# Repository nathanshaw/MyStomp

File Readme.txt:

ReadMe file for the MyStomp Project

To Do :

Flags to use 

--dac:3
--adc:3
--c1
--adaptive:256
--srate 44100

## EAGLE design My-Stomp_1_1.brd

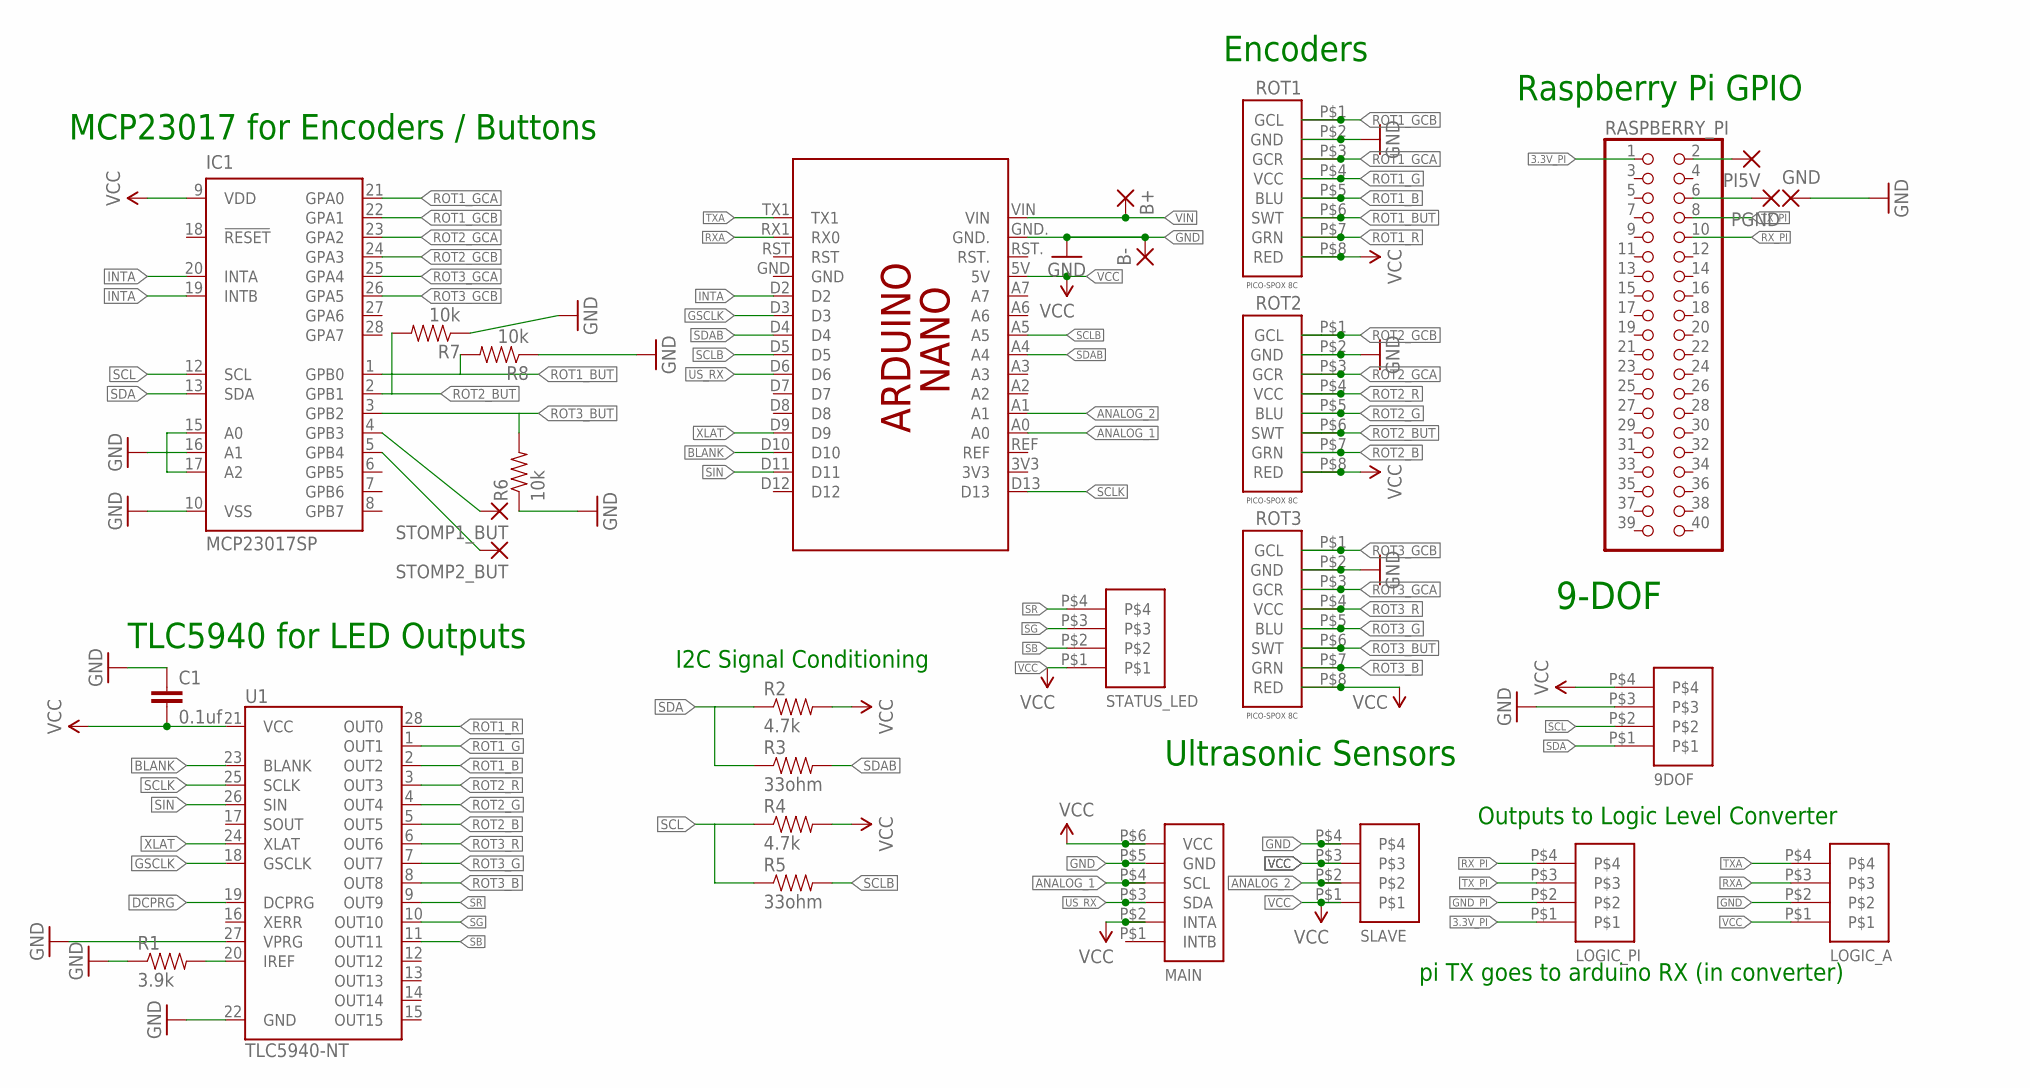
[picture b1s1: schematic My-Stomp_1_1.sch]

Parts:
9DOF: PICO_SPOX_4C
B+: 2,15/1,0
B-: 2,15/1,0
C1: 0.1uf; CAP-PTH-5MM
GND: 2,15/1,0
IC1: MCP23017SP; DIL28-3
LOGIC_A: PICO_SPOX_4C
LOGIC_PI: PICO_SPOX_4C
MAIN: PICO_SPOX_6C
PCB2: ARDUINO_NANO
PGND: 2,15/1,0
PI5V: 2,15/1,0
R1: 3.9k; AXIAL-0.3
R2, R4: 4.7k; AXIAL-0.3
R3, R5: 33ohm; AXIAL-0.3
R6, R7, R8: 10k; AXIAL-0.3
RASPBERRY_PI: PINHD-2X20; 2X20
ROT1, ROT2, ROT3: PICO_SPOX_8C; PICO_SPOC_8C
SLAVE: PICO_SPOX_4C
STATUS_LED: PICO_SPOX_4C
STOMP1_BUT, STOMP2_BUT: 2,15/1,0
U1: TLC5940-NT; DIL28-3

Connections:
3.3V_PI: LOGIC_PI.P$1, RASPBERRY_PI.1
ANALOG_1: MAIN.P$4 (SCL), PCB2.A0
ANALOG_2: PCB2.A1, SLAVE.P$2
BLANK: PCB2.D10, U1.23 (BLANK)
DCPRG: U1.19 (DCPRG)
GND: 9DOF.P$3, B-.1, C1.1, GND.1, IC1.10 (VSS), IC1.15 (A0), IC1.16 (A1), IC1.17 (A2), LOGIC_A.P$2, MAIN.P$5 (GND), PCB2.GND., R1.P$1 (1), R6.P$1 (1), R7.P$1 (1), R8.P$1 (1), ROT1.P$2 (GND), ROT2.P$2 (GND), ROT3.P$2 (GND), SLAVE.P$4, U1.22 (GND), U1.27 (VPRG)
GND_PI: LOGIC_PI.P$2, PGND.1, RASPBERRY_PI.6
GSCLK: PCB2.D3, U1.18 (GSCLK)
INTA: IC1.19 (INTB), IC1.20 (INTA), PCB2.D2
unnamed: IC1.4 (GPB3), STOMP1_BUT.1
unnamed: IC1.5 (GPB4), STOMP2_BUT.1
unnamed: PI5V.1, RASPBERRY_PI.2
unnamed: R1.P$2 (2), U1.20 (IREF)
ROT1_B: ROT1.P$5 (BLU), U1.2 (OUT2)
ROT1_BUT: IC1.1 (GPB0), R8.P$2 (2), ROT1.P$6 (SWT)
ROT1_G: ROT1.P$4 (VCC), U1.1 (OUT1)
ROT1_GCA: IC1.21 (GPA0), ROT1.P$3 (GCR)
ROT1_GCB: IC1.22 (GPA1), ROT1.P$1 (GCL)
ROT1_R: ROT1.P$7 (GRN), U1.28 (OUT0)
ROT2_B: ROT2.P$7 (GRN), U1.5 (OUT5)
ROT2_BUT: IC1.2 (GPB1), R7.P$2 (2), ROT2.P$6 (SWT)
ROT2_G: ROT2.P$5 (BLU), U1.4 (OUT4)
ROT2_GCA: IC1.23 (GPA2), ROT2.P$3 (GCR)
ROT2_GCB: IC1.24 (GPA3), ROT2.P$1 (GCL)
ROT2_R: ROT2.P$4 (VCC), U1.3 (OUT3)
ROT3_B: ROT3.P$7 (GRN), U1.8 (OUT8)
ROT3_BUT: IC1.3 (GPB2), R6.P$2 (2), ROT3.P$6 (SWT)
ROT3_G: ROT3.P$5 (BLU), U1.7 (OUT7)
ROT3_GCA: IC1.25 (GPA4), ROT3.P$3 (GCR)
ROT3_GCB: IC1.26 (GPA5), ROT3.P$1 (GCL)
ROT3_R: ROT3.P$4 (VCC), U1.6 (OUT6)
RXA: LOGIC_A.P$3, PCB2.RX1 (RX0)
RX_PI: LOGIC_PI.P$4, RASPBERRY_PI.10
SB: STATUS_LED.P$2, U1.11 (OUT11)
SCL: 9DOF.P$2, IC1.12 (SCL), R4.P$1 (1), R5.P$1 (1)
SCLB: PCB2.A5, PCB2.D5, R5.P$2 (2)
SCLK: PCB2.D13, U1.25 (SCLK)
SDA: 9DOF.P$1, IC1.13 (SDA), R2.P$1 (1), R3.P$1 (1)
SDAB: PCB2.A4, PCB2.D4, R3.P$2 (2)
SG: STATUS_LED.P$3, U1.10 (OUT10)
SIN: PCB2.D11, U1.26 (SIN)
SR: STATUS_LED.P$4, U1.9 (OUT9)
TXA: LOGIC_A.P$4, PCB2.TX1
TX_PI: LOGIC_PI.P$3, RASPBERRY_PI.8
US_RX: MAIN.P$3 (SDA), PCB2.D6
VCC: 9DOF.P$4, C1.2, IC1.9 (VDD), LOGIC_A.P$1, MAIN.P$2 (INTA), MAIN.P$6 (VCC), PCB2.5V, R2.P$2 (2), R4.P$2 (2), ROT1.P$8 (RED), ROT2.P$8 (RED), ROT3.P$8 (RED), SLAVE.P$1, SLAVE.P$3, STATUS_LED.P$1, U1.21 (VCC)
VIN: B+.1, PCB2.VIN
XLAT: PCB2.D9, U1.24 (XLAT)

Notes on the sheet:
I2C Signal Conditioning
TLC5940 for LED Outputs
MCP23017 for Encoders / Buttons
Ultrasonic Sensors
9-DOF
pi TX goes to arduino RX (in converter)
Outputs to Logic Level Converter
Raspberry Pi GPIO
Encoders

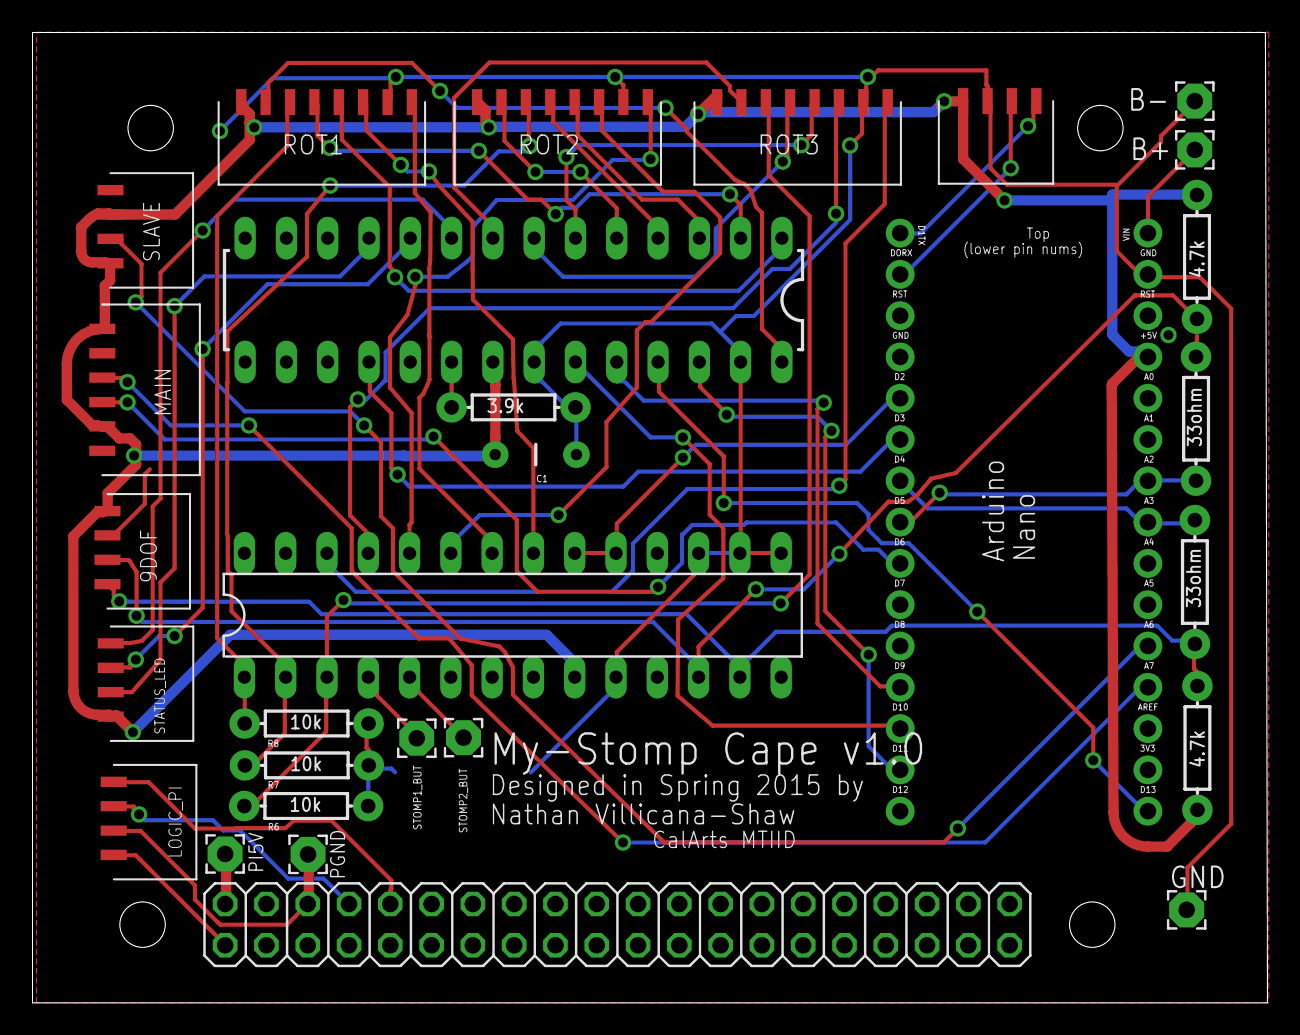
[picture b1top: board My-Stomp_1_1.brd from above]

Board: 2 copper layers, 76.0 x 59.7 mm, 29 parts (0 on the bottom side), 47 nets.

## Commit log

2015-02-09 Basic Framework for FX added
2015-02-09 Sewing things together more, added recording
2015-02-09 Everything Works, Stable Build
2015-02-09 Added 3d models and presentations
2015-02-09 Finished Presentation
2015-02-09 Added images for presentations and more
2015-02-23 Added Firmware folder
2015-02-23 test script added for FX
2015-02-23 Code for Ultrasonics Updated
    need to apply medium filter to ultrasonics for better readings
2015-02-23 Added MCP test file (untested)
2015-02-23 Another test file
2015-02-23 tweaked firmware a bit
2015-02-24 Crosstalk Folder and Code Added
    The crosstalk folder is for sketches that test the arduino/raspberry pi
    communication loop
2015-02-24 added spin test code
2015-02-24 added Readme file and got git on pi working
2015-02-24 9dof firmware added
2015-02-25 Untested mcl code added
2015-02-25 added working mcl code
2015-02-26 added more code
2015-02-27 code to test encoders added
2015-02-28 Started Master Code
    With startup modes
2015-03-01 Started Merging Code
2015-03-02 Got working modes
    for boot and long pressed and controller upside down
2015-03-03 Clean-up
    got rid of outdated code
2015-03-04 added pi test code
2015-03-04 got working pi code - for testing
2015-03-04 fix a bug
2015-03-07 tweaking
2015-03-07 Sound is Flowing
2015-03-07 program 1 is clean and reverb
2015-03-07 fixed bug
2015-03-07 bug fix again
2015-03-07 test all ghubgraphs
2015-03-07 update test
2015-03-07 bug fix
2015-03-07 recording test
2015-03-07 scale back
2015-03-07 recorder test again
2015-03-07 scaled gain
2015-03-07 ecording Successful!!!
2015-03-08 some updates
2015-03-08 Some Changes
2015-03-09 fixed negative numbers using serial
2015-03-09 port number change
2015-03-09 added adaptive recording naming
2015-03-09 Updated firmware to send negative numbers
2015-03-09 sds sd
2015-03-09 Merge remote-tracking branch 'origin/master'
    Conflicts:
    chuck/Chorus_0.1.ck
    chuck/Clean_0.1.ck
    chuck/Echo_0.1.ck
    chuck/Expander_0.1.ck
    chuck/Initalize_myStomp.ck
2015-03-09 testing time
2015-03-09 typo fix
2015-03-09 nothing change
2015-03-09 Added guitar mode
2015-03-13 robot code added
    also started creating optimized version of the code
2015-03-26 The nightmare continues
2015-03-29 Added test code for arduino
2015-03-31 Added NIME paper
2015-04-07 MyBand Stuff Added
2015-04-12 NIME stuff added
2015-04-26 Added more work to NIME paper
2016-05-24 a few minor eagle changes

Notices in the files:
parts and their libraries:
SparkFun-DigitalIC: Licensing: Creative Commons ShareAlike 4.0 International - https://creativecommons.org/licenses/by-sa/4.0
